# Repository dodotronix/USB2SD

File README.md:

# Bridge - USB TO SD Card 
This project is originally for 3d printer Anet. As the movement of the extruder
is shredded, when printing via USB serial connection. The shredding can be
avoided, when printing from the SDcard. This is not so confortable, because the
card has to be unplugged, inserted into the card reader to store the print data
and returned to the printer.

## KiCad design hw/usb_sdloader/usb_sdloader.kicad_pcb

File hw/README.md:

# HW design notes

## BOM list
| Component name  | Type | Purchase | Notes |
| :---: | :---:| :---: | :---: |
| [SN3257QPWRQ1](https://cz.mouser.com/ProductDetail/Texas-Instruments/SN3257QPWRQ1?qs=%252B6g0mu59x7JRD99NE57pzA%3D%3D) | analog mux | :white_square_button: | |
| [10118194-0001LF](https://cz.mouser.com/ProductDetail/Amphenol-FCI/10118194-0001LF?qs=Ywefl8B65e4FIdY8OWfRQA%3D%3D) | usb connector SMD | :white_square_button: | | 
| [TOL-09419](https://cz.mouser.com/ProductDetail/SparkFun/TOL-09419?qs=WyAARYrbSnZj2Gc3mUSwiw%3D%3D) | sd sniffer | :white_square_button: | |
| [USB2642-I/ML](https://cz.mouser.com/ProductDetail/Microchip-Technology/USB2642-I-ML?qs=QaDcGzfVzPPIqPyBH4Ei1Q%3D%3D) | usb bridge | :white_square_button: | |

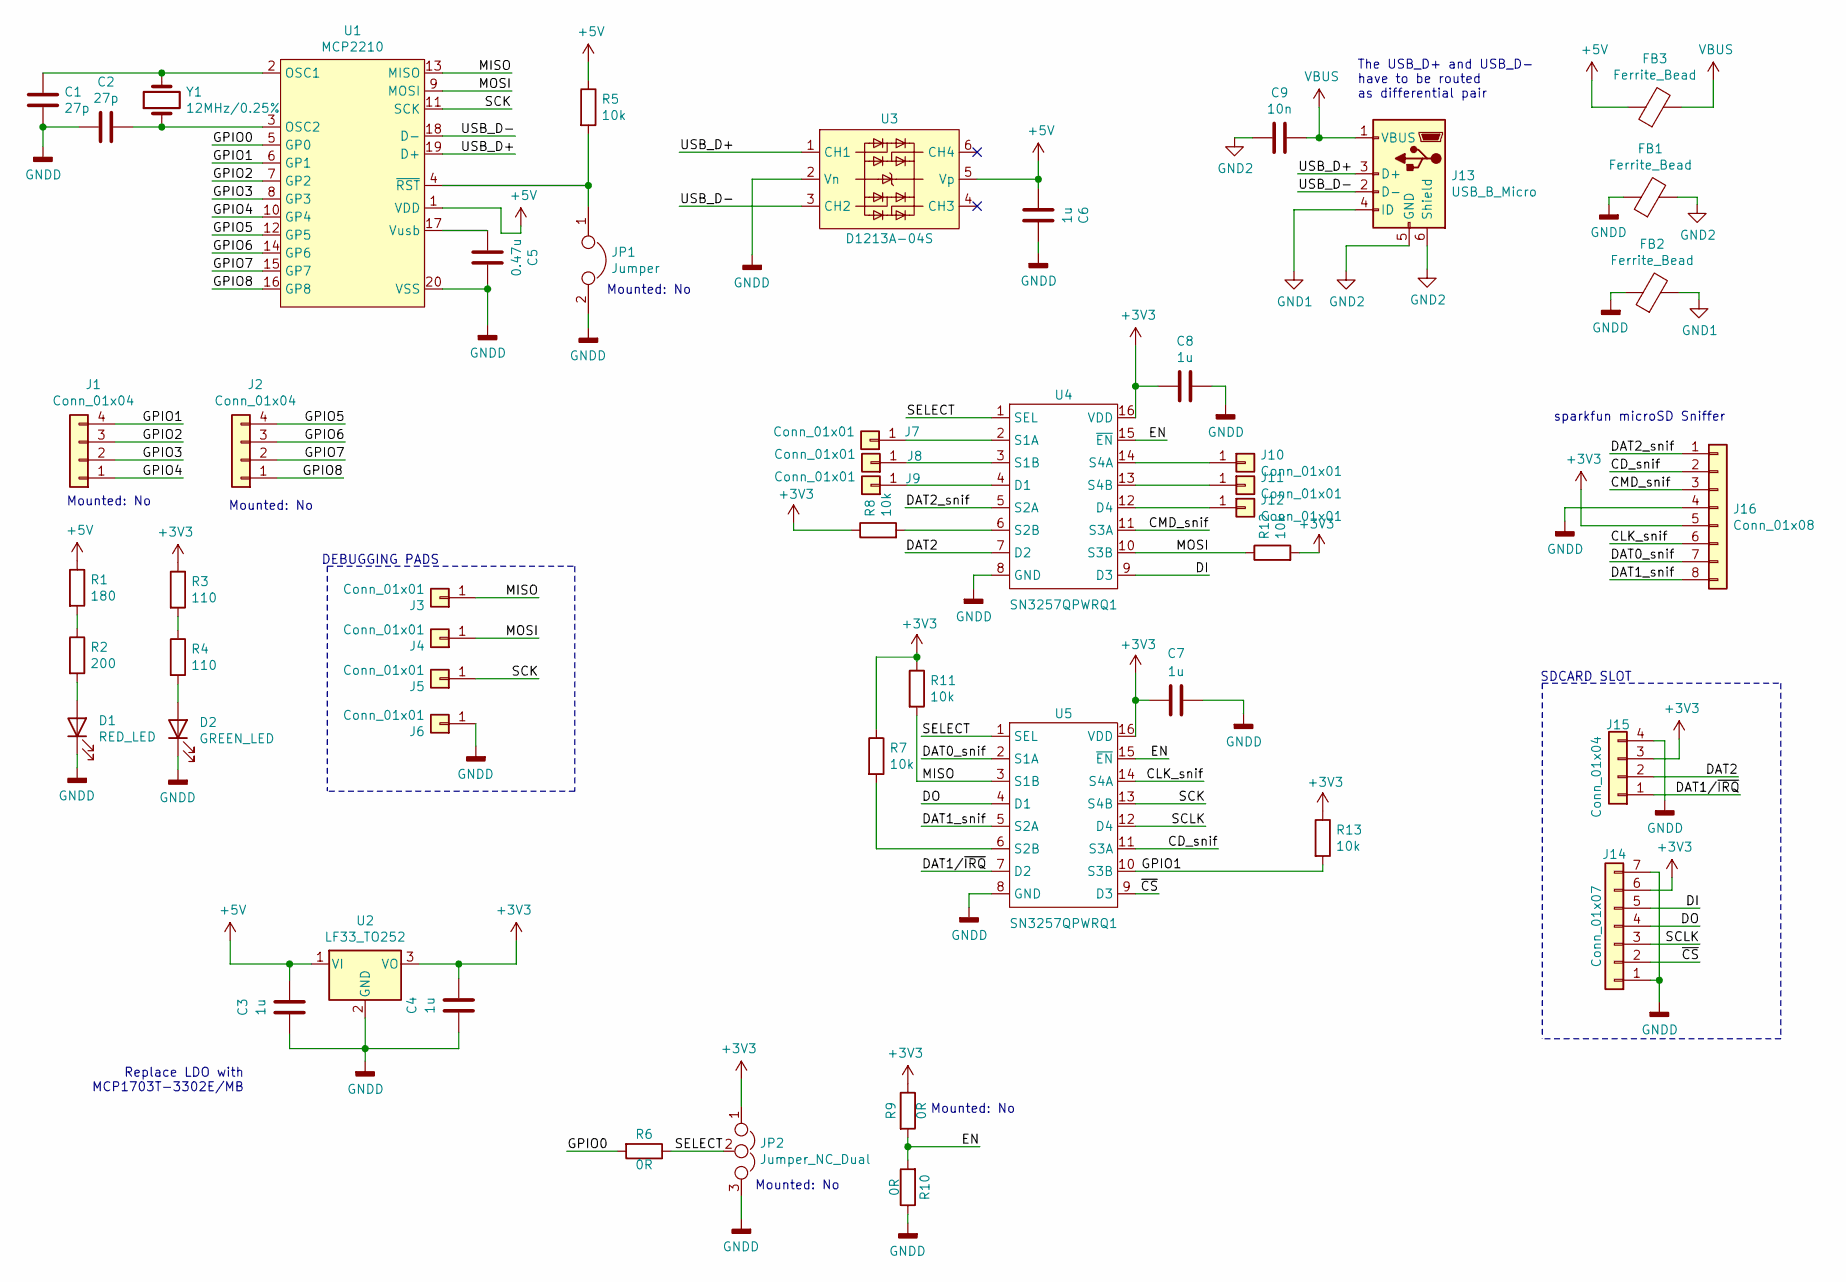
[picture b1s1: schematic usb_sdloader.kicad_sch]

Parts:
C1, C2: 27p; C_0805_2012Metric_Pad1.18x1.45mm_HandSolder
C3, C4, C6, C7, C8: 1u; C_0805_2012Metric_Pad1.18x1.45mm_HandSolder
C5: 0.47u; C_0805_2012Metric_Pad1.18x1.45mm_HandSolder
C9: 10n; C_0603_1608Metric_Pad1.08x0.95mm_HandSolder
D1: RED_LED; LED_1206_3216Metric_Pad1.42x1.75mm_HandSolder
D2: GREEN_LED; LED_1206_3216Metric_Pad1.42x1.75mm_HandSolder
FB1, FB2, FB3: Ferrite_Bead; L_0603_1608Metric_Pad1.05x0.95mm_HandSolder
J1, J2, J15: Conn_01x04; PinHeader_1x04_P2.54mm_Vertical_SMD_Pin1Left
J3, J4, J5, J6, J7, J8, J9, J10, J11, J12: Conn_01x01; TestPoint_Pad_D2.0mm
J13: USB_B_Micro; USB_Micro-B_Molex-105017-0001
J14: Conn_01x07; PinHeader_1x07_P2.54mm_Vertical_SMD_Pin1Left
J16: Conn_01x08; PinHeader_1x08_P2.54mm_Vertical_SMD_Pin1Left
JP1: Jumper; PinHeader_1x02_P2.54mm_Vertical_SMD_Pin1Left
JP2: Jumper_NC_Dual; PinHeader_1x03_P2.54mm_Vertical_SMD_Pin1Left
R1: 180; R_0805_2012Metric_Pad1.20x1.40mm_HandSolder
R2: 200; R_0805_2012Metric_Pad1.20x1.40mm_HandSolder
R3, R4: 110; R_0805_2012Metric_Pad1.20x1.40mm_HandSolder
R5, R7, R8, R11, R12, R13: 10k; R_0805_2012Metric_Pad1.20x1.40mm_HandSolder
R6, R9, R10: 0R; R_0603_1608Metric_Pad0.98x0.95mm_HandSolder
U1: MCP2210; SOIC-20W_7.5x12.8mm_P1.27mm
U2: LF33_TO252; TO-252-2
U3: D1213A-04S; SOT-363_SC-70-6_Handsoldering
U4, U5: SN3257QPWRQ1; TSSOP-16_4.4x5mm_P0.65mm
Y1: 12MHz/0.25%; Crystal_SMD_HC49-SD_HandSoldering

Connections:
+3V3: C4.1, C7.2, C8.2, J14.6, J15.3, J16.5, JP2.1, R3.1, R7.1, R8.1, R9.1, R11.1, R12.2, R13.1, U2.3 (VO), U4.16 (VDD), U5.16 (VDD)
+5V: C3.1, C6.2, FB3.1, R1.1, R5.1, U1.1 (VDD), U2.1 (VI), U3.5 (Vp)
/CD_snif: J16.2, U5.11 (S3A)
/CLK_snif: J16.6, U5.14 (S4A)
/CMD_snif: J16.3, U4.11 (S3A)
/DAT0_snif: J16.7, U5.2 (S1A)
/DAT1_snif: J16.8, U5.5 (S2A)
/DAT1/~IRQ: J15.1, U5.7 (D2)
/DAT2: J15.2, U4.7 (D2)
/DAT2_snif: J16.1, U4.5 (S2A)
/DI: J14.5, U4.9 (D3)
/DO: J14.4, U5.4 (D1)
/EN: R9.2, R10.2, U4.15 (~EN), U5.15 (~EN)
/GPIO0: R6.2, U1.5 (GP0)
/GPIO1: J1.4, R13.2, U1.6 (GP1), U5.10 (S3B)
/GPIO2: J1.3, U1.7 (GP2)
/GPIO3: J1.2, U1.8 (GP3)
/GPIO4: J1.1, U1.10 (GP4)
/GPIO5: J2.4, U1.12 (GP5)
/GPIO6: J2.3, U1.14 (GP6)
/GPIO7: J2.2, U1.15 (GP7)
/GPIO8: J2.1, U1.16 (GP8)
/MISO: J3.1, R11.2, U1.13 (MISO), U5.3 (S1B)
/MOSI: J4.1, R12.1, U1.9 (MOSI), U4.10 (S3B)
/SCK: J5.1, U1.11 (SCK), U5.13 (S4B)
/SCLK: J14.3, U5.12 (D4)
/SELECT: JP2.2, R6.1, U4.1 (SEL), U5.1 (SEL)
/USB_D+: J13.3 (D+), U1.19 (D+), U3.1 (CH1)
/USB_D-: J13.2 (D-), U1.18 (D-), U3.3 (CH2)
/~CS: J14.2, U5.9 (D3)
GND1: FB2.2, J13.4 (ID)
GND2: C9.2, FB1.2, J13.5 (GND), J13.6 (Shield)
GNDD: C1.2, C2.1, C3.2, C4.2, C5.1, C6.1, C7.1, C8.1, D1.1 (K), D2.1 (K), FB1.1, FB2.1, J6.1, J14.1, J14.7, J15.4, J16.4, JP1.2, JP2.3, R10.1, U1.20 (VSS), U2.2 (GND), U3.2 (Vn), U4.8 (GND), U5.8 (GND)
unnamed: C1.1, U1.2 (OSC1), Y1.2
unnamed: C2.2, U1.3 (OSC2), Y1.1
unnamed: C5.2, U1.17 (Vusb)
unnamed: D1.2 (A), R2.2
unnamed: D2.2 (A), R4.2
unnamed: J7.1, U4.2 (S1A)
unnamed: J8.1, U4.3 (S1B)
unnamed: J9.1, U4.4 (D1)
unnamed: J10.1, U4.14 (S4A)
unnamed: J11.1, U4.13 (S4B)
unnamed: J12.1, U4.12 (D4)
unnamed: JP1.1, R5.2, U1.4 (~RST)
unnamed: R1.2, R2.1
unnamed: R3.2, R4.1
unnamed: R7.2, U5.6 (S2B)
unnamed: R8.2, U4.6 (S2B)
VBUS: C9.1, FB3.2, J13.1 (VBUS)

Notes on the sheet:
Mounted: No
Replace LDO with MCP1703T-3302E/MB
DEBUGGING PADS
The USB_D+ and USB_D- have to be routed as differential pair
SDCARD SLOT
sparkfun microSD Sniffer

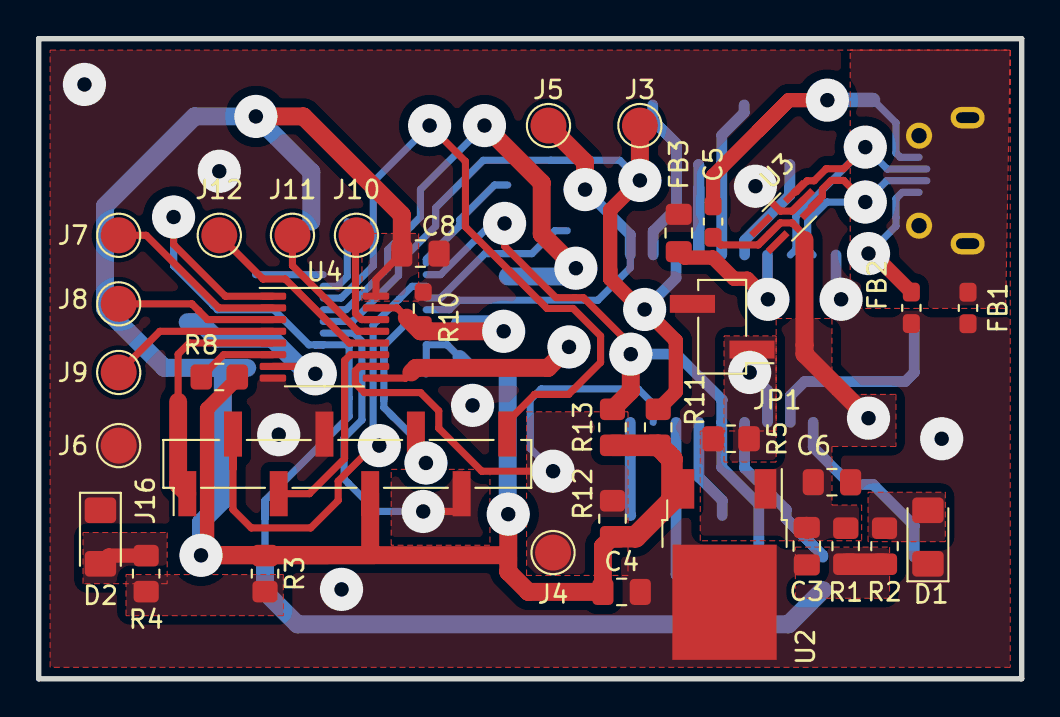
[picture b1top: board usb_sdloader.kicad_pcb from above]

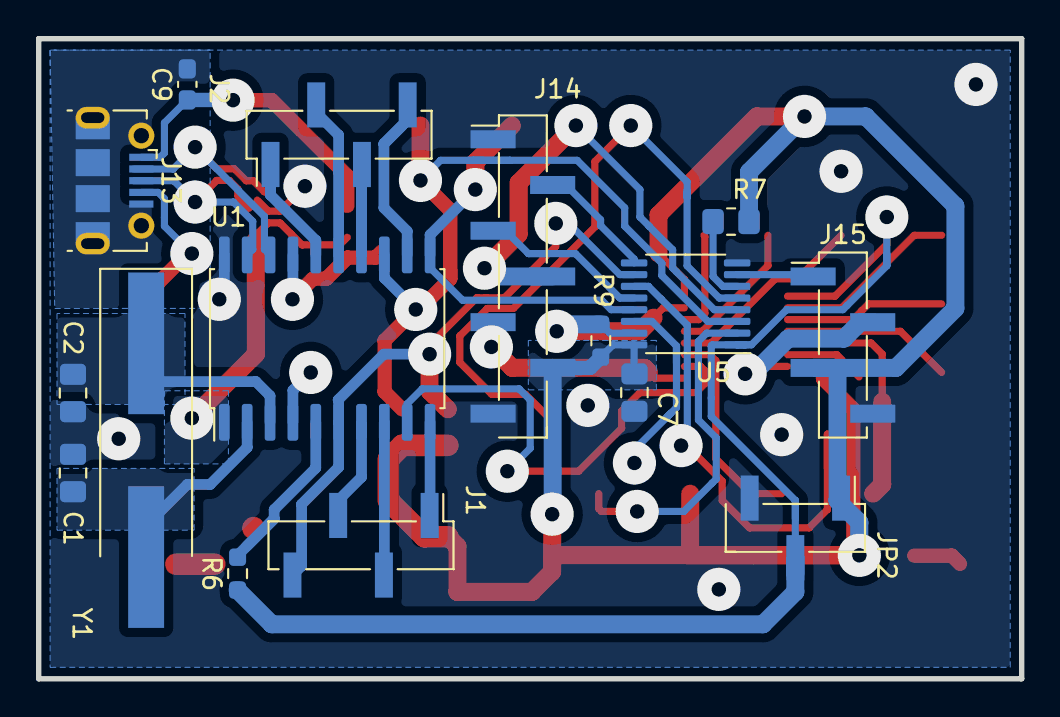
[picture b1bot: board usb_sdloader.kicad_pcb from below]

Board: 2 copper layers, 54.6 x 35.6 mm, 51 parts (16 on the bottom side), 50 nets.

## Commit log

2022-05-29 new readme
2022-05-29 corrected heading in README
2022-05-29 ignore kicad zip files
2022-05-29 new kicad project
2022-05-29 readme for the HW part - BOOM list
2022-05-29 outputs for fabrication
2022-12-10 added basic module structure, which will be probably needed - not implemented
